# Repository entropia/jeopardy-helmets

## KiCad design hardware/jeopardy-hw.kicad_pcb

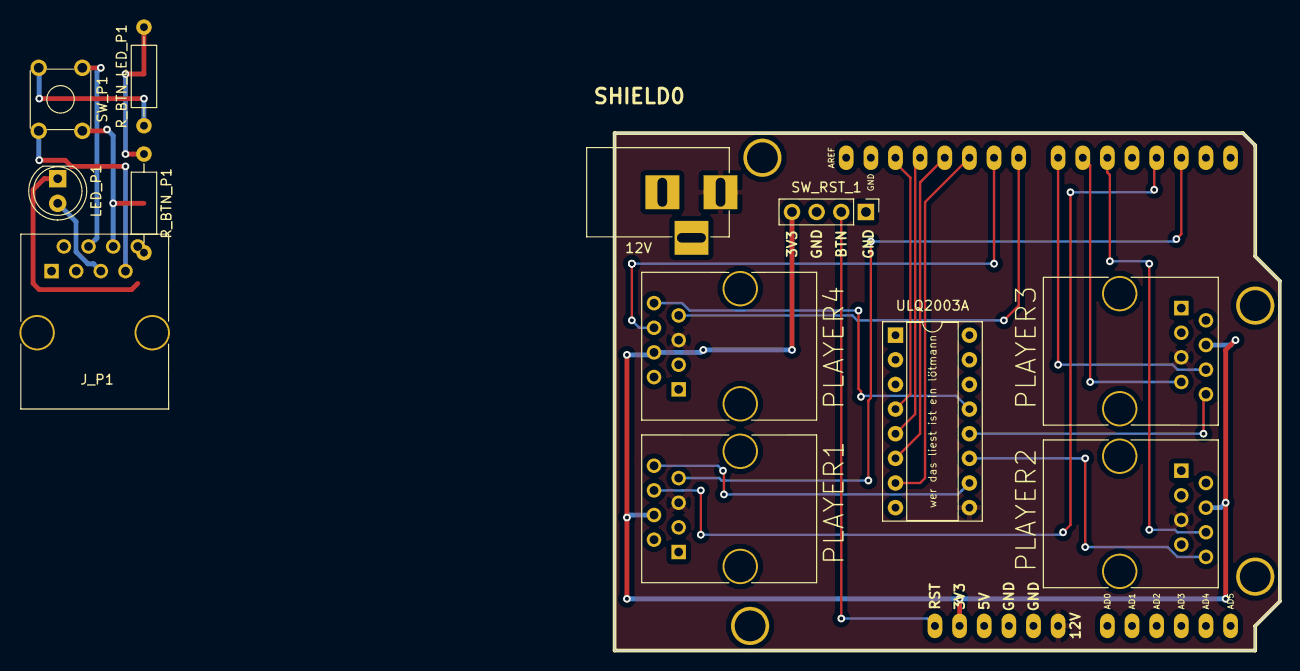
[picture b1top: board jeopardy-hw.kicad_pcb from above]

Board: 2 copper layers, 68.6 x 53.3 mm, 13 parts (0 on the bottom side), 24 nets.

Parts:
12V: Barrel_Jack_Switch; BARREL_JACK
J_P1: RJ45; RJ45_8
LED_P1: LED_Series; LED_D5.0mm
PLAYER1, PLAYER2, PLAYER3, PLAYER4: RJ45; RJ45_8
R_BTN_LED_P1: 150; R_Axial_DIN0207_L6.3mm_D2.5mm_P10.16mm_Horizontal
R_BTN_P1: 10k; R_Axial_DIN0207_L6.3mm_D2.5mm_P10.16mm_Horizontal
SHIELD0: ARDUINO_SHIELD; ARDUINO SHIELD
SW_P1: SW_Push_LED; SW_TH_Tactile_Omron_B3F-10xx
SW_RST_1: SW_Push_LED; Pin_Header_Straight_1x04_Pitch2.54mm
ULQ2003A: ULQ2003A; DIP-16_W7.62mm_Socket

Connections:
+3V3: J_P1.4, PLAYER1.4, PLAYER2.4, PLAYER3.4, PLAYER4.4, SHIELD0.3V3, SW_P1.1, SW_RST_1.4
+12V: 12V.1, J_P1.5, LED_P1.2, PLAYER1.5, PLAYER2.5, PLAYER3.5, PLAYER4.5, SHIELD0.V_IN, ULQ2003A.9
GND: 12V.2, J_P1.1, PLAYER1.1, PLAYER2.1, PLAYER3.1, PLAYER4.1, R_BTN_LED_P1.2, R_BTN_P1.1, SHIELD0.GND1, SHIELD0.GND2, SHIELD0.GND3, SW_RST_1.1, ULQ2003A.8
unnamed: PLAYER1.6, SHIELD0.3
unnamed: PLAYER1.7, SHIELD0.2
unnamed: PLAYER1.8, ULQ2003A.10
unnamed: PLAYER2.6, SHIELD0.5
unnamed: PLAYER2.7, SHIELD0.4
unnamed: PLAYER2.8, ULQ2003A.11
unnamed: PLAYER3.6, SHIELD0.7
unnamed: PLAYER3.7, SHIELD0.6
unnamed: PLAYER3.8, ULQ2003A.12
unnamed: PLAYER4.6, SHIELD0.9
unnamed: PLAYER4.7, SHIELD0.8
unnamed: PLAYER4.8, ULQ2003A.13
unnamed: J_P1.6, R_BTN_P1.2, SW_P1.2
unnamed: J_P1.7, SW_P1.4
unnamed: J_P1.8, LED_P1.1
unnamed: R_BTN_LED_P1.1, SW_P1.3
unnamed: SHIELD0.10, ULQ2003A.7
unnamed: SHIELD0.11, ULQ2003A.6
unnamed: SHIELD0.12, ULQ2003A.5
unnamed: SHIELD0.13, ULQ2003A.4
unnamed: SHIELD0.RST, SW_RST_1.2

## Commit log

2023-11-11 One commit to rule them all
2023-11-11 Add the hardware schematics
